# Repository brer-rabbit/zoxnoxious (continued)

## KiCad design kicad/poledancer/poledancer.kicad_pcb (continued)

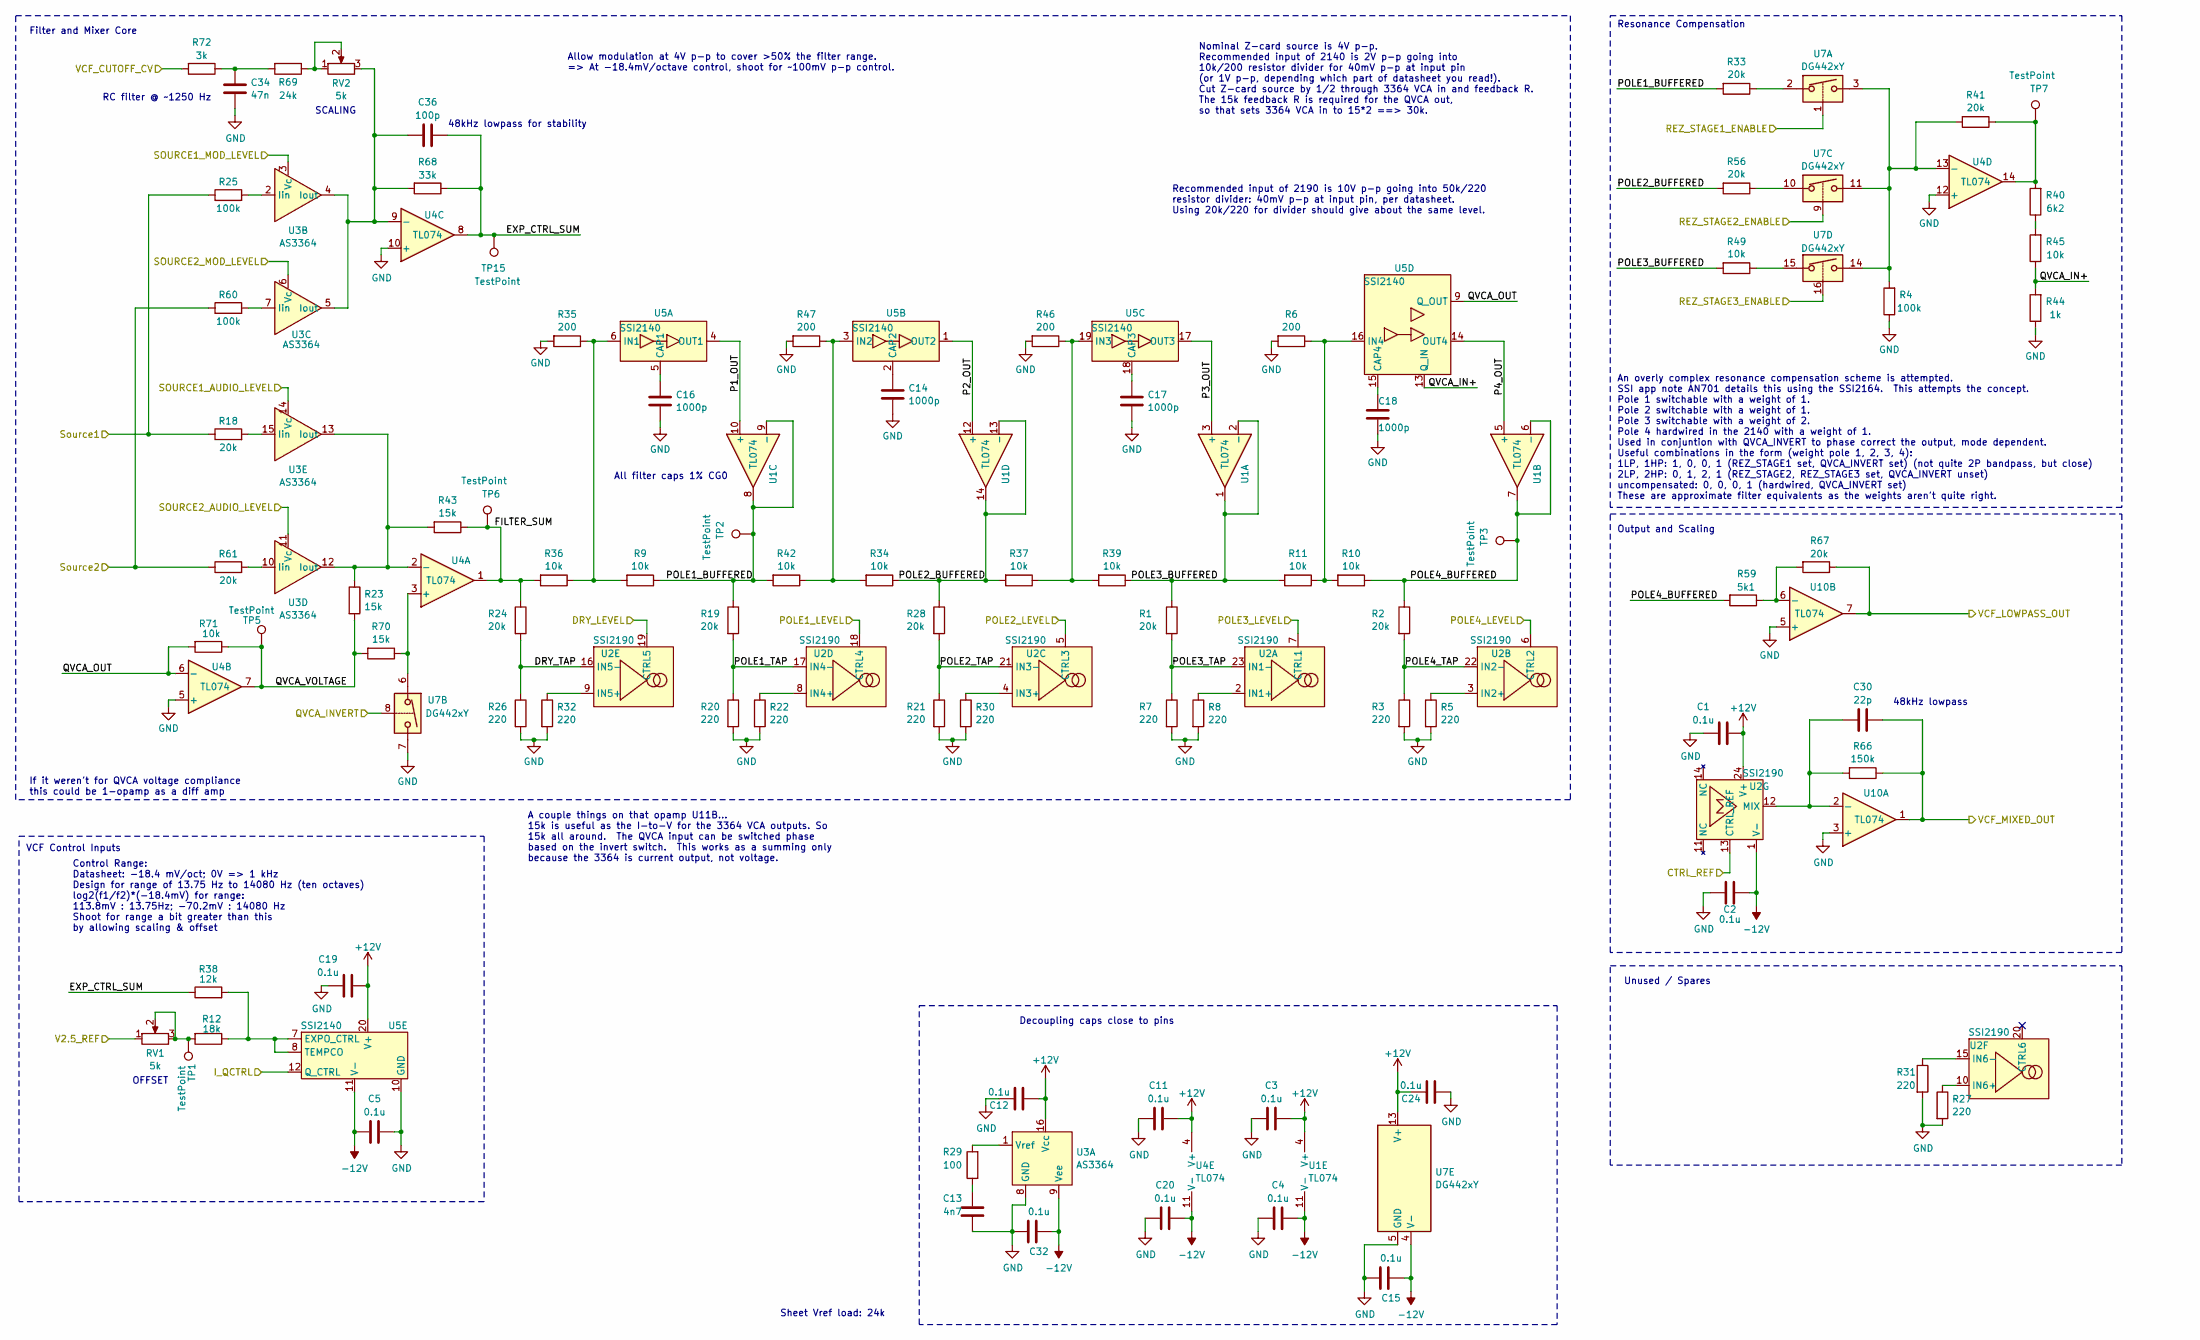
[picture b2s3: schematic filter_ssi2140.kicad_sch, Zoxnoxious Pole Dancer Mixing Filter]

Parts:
C1, C2, C3, C4, C5, C11, C12, C15, C19, C20, C24, C32: 0.1u; C_0603_1608Metric; LCSC C14663
C13: 4n7; C_0603_1608Metric; LCSC C53987
C14, C16, C17, C18: 1000p; C_0805_2012Metric; Digikey 478-KGM21BCG1H102FTCT-ND
C30: 22p; C_0603_1608Metric; LCSC C1653
C34: 47n; C_0603_1608Metric; LCSC C1622
C36: 100p; C_0603_1608Metric; LCSC C14858
R1, R2, R18, R19, R24, R28, R33, R41, R56, R61, R67: 20k; R_0603_1608Metric; LCSC C4184
R3, R5, R7, R8, R20, R21, R22, R26, R27, R30, R31, R32: 220; R_0603_1608Metric; LCSC C22962
R4, R25, R60: 100k; R_0603_1608Metric; LCSC C25803
R6, R35, R46, R47: 200; R_0603_1608Metric; LCSC C8218
R9, R10, R11, R34, R36, R37, R39, R42, R45, R49, R71: 10k; R_0603_1608Metric; LCSC C25804
R12: 18k; R_0603_1608Metric; LCSC C25810
R23, R43, R70: 15k; R_0603_1608Metric; LCSC C22809
R29: 100; R_0603_1608Metric; LCSC C22775
R38: 12k; R_0603_1608Metric; LCSC C22790
R40: 6k2; R_0603_1608Metric; LCSC C4260
R44: 1k; R_0603_1608Metric; LCSC C21190
R59: 5k1; R_0603_1608Metric; LCSC C23186
R66: 150k; R_0603_1608Metric; LCSC C22807
R68: 33k; R_0603_1608Metric; LCSC C4216
R69: 24k; R_0603_1608Metric; LCSC C23352
R72: 3k; R_0603_1608Metric; LCSC C4211
RV1, RV2: 5k; Potentiometer_Bourns_3296W_Vertical
TP1, TP2, TP3, TP5, TP6, TP7, TP15: TestPoint; TestPoint_Pad_2.0x2.0mm
U1, U4, U10: TL074; TSSOP-14_4.4x5mm_P0.65mm; LCSC C96507
U2: SSI2190; SSOP-24_3.9x8.7mm_P0.635mm
U3: AS3364; SOIC-16_3.9x9.9mm_P1.27mm
U5: SSI2140; SSOP-20_4.4x6.5mm_P0.65mm
U7: DG442xY; SOIC-16_3.9x9.9mm_P1.27mm; LCSC C2673321

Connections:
+12V: C1.1, C3.1, C11.1, C12.1, C19.1, C24.2, U1.4 (V+), U2.24 (V+), U3.16 (Vcc), U4.4 (V+), U5.20 (V+), U7.13 (V+); also elsewhere on the board
-12V: C2.1, C4.1, C5.2, C15.1, C20.1, C32.1, U1.11 (V-), U2.1 (V-), U3.9 (Vee), U4.11 (V-), U5.11 (V-), U7.4 (V-); also elsewhere on the board
/CTRL_REF: U2.13 (CTRL_REF); also elsewhere on the board
/DRY_LEVEL: U2.19 (CTRL5); also elsewhere on the board
/INPUT1: R18.1, R25.1; also elsewhere on the board
/INPUT2: R60.1, R61.1; also elsewhere on the board
/POLE1_LEVEL: U2.18 (CTRL4); also elsewhere on the board
/POLE2_LEVEL: U2.5 (CTRL3); also elsewhere on the board
/POLE3_LEVEL: U2.7 (CTRL1); also elsewhere on the board
/POLE4_LEVEL: U2.6 (CTRL2); also elsewhere on the board
/QCTRL_CURRENT: U5.12 (Q_CTRL); also elsewhere on the board
/QVCA_INVERT: U7.8; also elsewhere on the board
/REZ_STAGE1_EN: U7.1; also elsewhere on the board
/REZ_STAGE2_EN: U7.9; also elsewhere on the board
/REZ_STAGE3_EN: U7.16; also elsewhere on the board
/SOURCE1_AUDIO_CV: U3.14 (Vc); also elsewhere on the board
/SOURCE1_MOD_CV: U3.3 (Vc); also elsewhere on the board
/SOURCE2_AUDIO_CV: U3.11 (Vc); also elsewhere on the board
/SOURCE2_MOD_CV: U3.6 (Vc); also elsewhere on the board
/VCF_CUTOFF_CV: R72.2; also elsewhere on the board
/VCF_RAW: R67.1, U10.7; also elsewhere on the board
/VREF_2.5V: RV1.1; also elsewhere on the board
/filter_ssi2140/DRY_TAP: R24.2, R26.1, U2.16 (IN5-)
/filter_ssi2140/EXP_CTRL_SUM: C36.2, R38.1, R68.1, TP15.1, U4.8
/filter_ssi2140/FILTER_SUM: R24.1, R36.2, R43.1, TP6.1, U4.1
/filter_ssi2140/P1_OUT: U1.10 (+), U5.4 (OUT1)
/filter_ssi2140/P2_OUT: U1.12 (+), U5.1 (OUT2)
/filter_ssi2140/P3_OUT: U1.3 (+), U5.17 (OUT3)
/filter_ssi2140/P4_OUT: U1.5 (+), U5.14 (OUT4)
/filter_ssi2140/POLE1_BUFFERED: R9.1, R19.1, R33.2, R42.2, TP2.1, U1.8, U1.9 (-)
/filter_ssi2140/POLE1_TAP: R19.2, R20.1, U2.17 (IN4-)
/filter_ssi2140/POLE2_BUFFERED: R28.1, R34.1, R37.2, R56.2, U1.13 (-), U1.14
/filter_ssi2140/POLE2_TAP: R21.1, R28.2, U2.21 (IN3-)
/filter_ssi2140/POLE3_BUFFERED: R1.1, R11.2, R39.1, R49.2, U1.1, U1.2 (-)
/filter_ssi2140/POLE3_TAP: R1.2, R7.1, U2.23 (IN1-)
/filter_ssi2140/POLE4_BUFFERED: R2.1, R10.1, R59.2, TP3.1, U1.6 (-), U1.7
/filter_ssi2140/POLE4_TAP: R2.2, R3.1, U2.22 (IN2-)
/filter_ssi2140/QVCA_IN+: R44.2, R45.1, U5.13 (Q_IN)
/filter_ssi2140/QVCA_OUT: R71.2, U4.6 (-), U5.9 (Q_OUT)
/filter_ssi2140/QVCA_VOLTAGE: R23.2, R70.2, R71.1, TP5.1, U4.7
/filter_ssi2140/VCF_MIXED_OUT: C30.1, R66.1, U10.1; also elsewhere on the board
GND: C1.2, C2.2, C3.2, C4.2, C5.1, C11.2, C12.2, C13.2, C14.2, C15.2, C16.2, C17.2, C18.2, C19.2, C20.2, C24.1, C32.2, C34.2, R3.2, R4.1, R5.2, R6.2, R7.2, R8.2, R20.2, R21.2, R22.2, R26.2, R27.2, R30.2, R31.2, R32.2, R35.2, R44.1, R46.2, R47.2, U3.8 (GND), U4.5 (+), U4.10 (+), U4.12 (+), U5.10 (GND), U7.5 (GND), U7.7, U10.3 (+), U10.5 (+); also elsewhere on the board
unnamed: C13.1, R29.1
unnamed: C34.1, R69.2, R72.1
unnamed: R12.2, RV1.2, RV1.3, TP1.1
unnamed: R33.1, U7.2
unnamed: R40.1, R45.2
unnamed: R40.2, R41.1, TP7.1, U4.14
unnamed: R49.1, U7.15
unnamed: R56.1, U7.10
unnamed: R69.1, RV2.1, RV2.2
unnamed: R8.1, U2.2 (IN1+)
unnamed: R5.1, U2.3 (IN2+)
unnamed: R30.1, U2.4 (IN3+)
unnamed: R22.1, U2.8 (IN4+)
unnamed: R32.1, U2.9 (IN5+)
unnamed: R27.1, U2.10 (IN6+)
unnamed: R31.1, U2.15 (IN6-)
unnamed: R29.2, U3.1 (Vref)
unnamed: R25.2, U3.2 (Iin)
unnamed: C36.1, R68.2, RV2.3, U3.4 (Iout), U3.5 (Iout), U4.9 (-)
unnamed: R60.2, U3.7 (Iin)
unnamed: R61.2, U3.10 (Iin)
unnamed: R23.1, R43.2, U3.12 (Iout), U3.13 (Iout), U4.2 (-)
unnamed: R18.2, U3.15 (Iin)
unnamed: R70.1, U4.3 (+), U7.6
unnamed: R4.2, R41.2, U4.13 (-), U7.3, U7.11, U7.14
unnamed: C16.1, U5.5 (CAP1)
unnamed: R9.2, R35.1, R36.1, U5.6 (IN1)
unnamed: C14.1, U5.2 (CAP2)
unnamed: R34.2, R42.1, R47.1, U5.3 (IN2)
unnamed: C17.1, U5.18 (CAP3)
unnamed: R37.1, R39.2, R46.1, U5.19 (IN3)
unnamed: C18.1, U5.15 (CAP4)
unnamed: R6.1, R10.2, R11.1, U5.16 (IN4)
unnamed: R12.1, R38.2, U5.7 (EXPO_CTRL), U5.8 (TEMPCO)
unnamed: C30.2, R66.2, U2.12 (MIX), U10.2 (-)
unnamed: R59.1, R67.2, U10.6 (-)

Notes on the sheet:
Nominal Z-card source is 4V p-p. Recommended input of 2140 is 2V p-p going into 10k/200 resistor divider for 40mV p-p at input pin (or 1V p-p, depending which part of datasheet you read!). Cut Z-card source by 1/2 through 3364 VCA in and feedback R. The 15k feedback R is required for the QVCA out, 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
Allow modulation at 4V p-p to cover >50% the filter range. => At -18.4mV/octave control, shoot for ~100mV p-p control.
OFFSET
Decoupling caps close to pins
RC filter @ ~1250 Hz
Sheet Vref load: 24k
An overly complex resonance compensation scheme is attempted. SSI app note AN701 details this using the SSI2164. This attempts the concept. Pole 1 switchable with a weight of 1. Pole 2 switchable with a weight of 1. Pole 3 switchable with a weight of 2. Pole 4 hardwired in the 2140 with a weight of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
VCF Control Inputs
Output and Scaling
48kHz lowpass for stability
Unused / Spares
Recommended input of 2190 is 10V p-p going into 50k/220 resistor divider: 40mV p-p at input pin, per datasheet. Using 20k/220 for divider should give about the same level.
Control Range: Datasheet: -18.4 mV/oct; 0V => 1 kHz Design for range of 13.75 Hz to 14080 Hz (ten octaves) log2(f1/f2)*(-18.4mV) for range: 113.8mV : 13.75Hz; -70.2mV : 14080 Hz Shoot for range a bit greater than this by allowing scaling & offset
If it weren't for QVCA voltage compliance this could be 1-opamp as a diff amp
All filter caps 1% CG0
Filter and Mixer Core
48kHz lowpass
SCALING
A couple things on that opamp U11B... 15k is useful as the I-to-V for the 3364 VCA outputs. So 15k all around. The QVCA input can be switched phase based on the invert switch. This works as a summing only because the 3364 is current output, not voltage.
Resonance Compensation

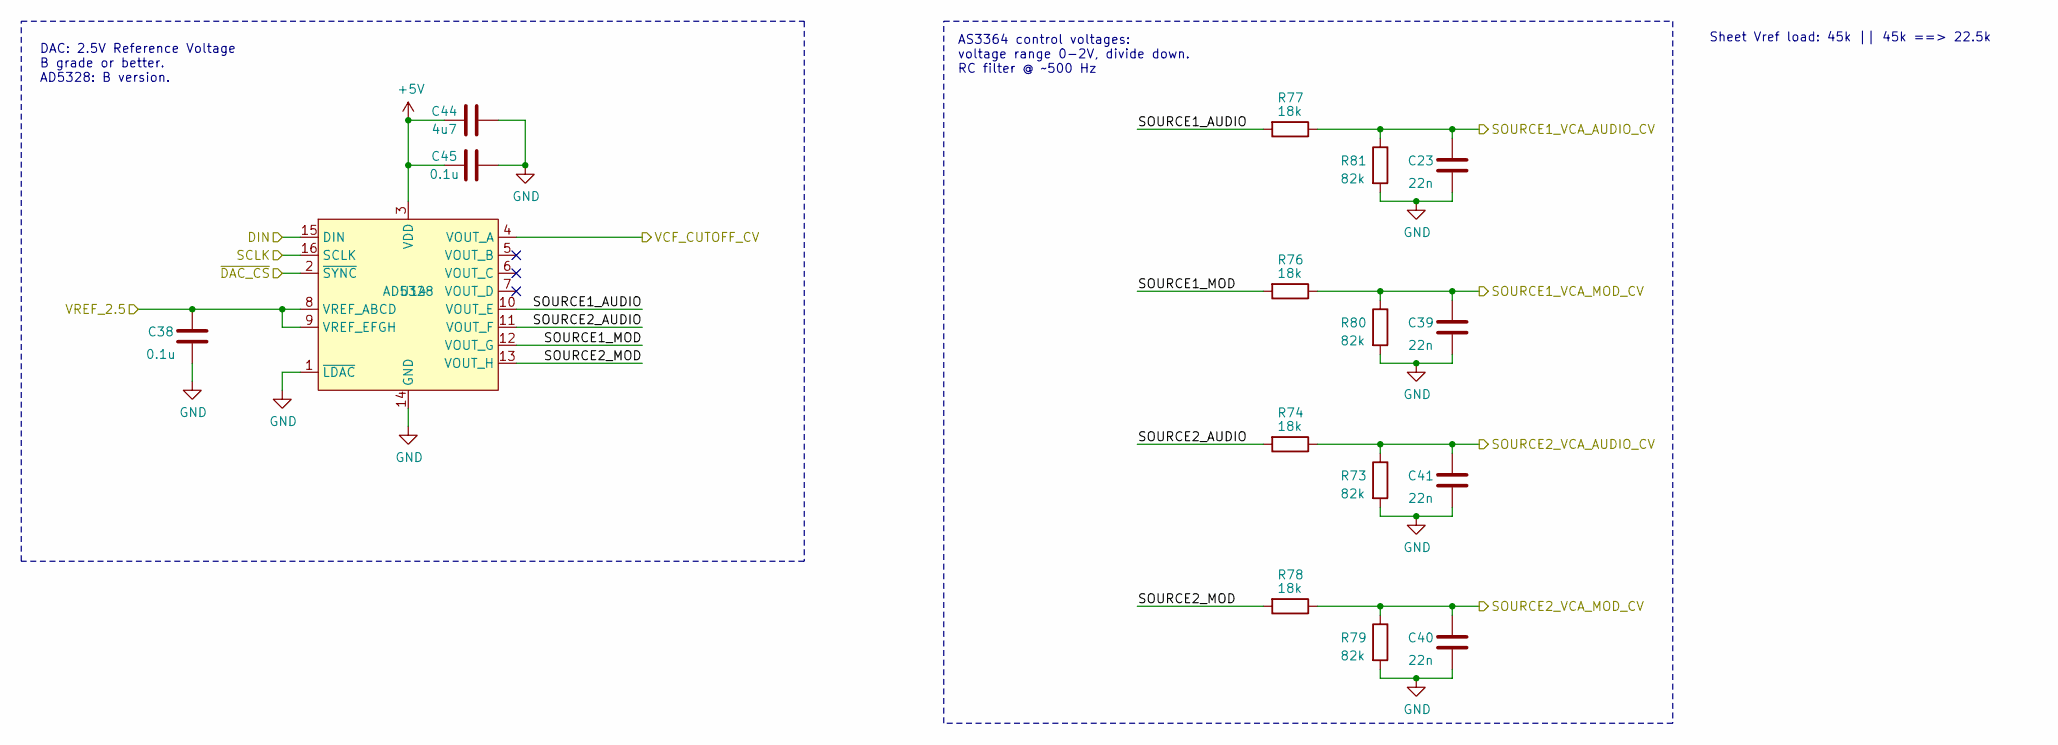
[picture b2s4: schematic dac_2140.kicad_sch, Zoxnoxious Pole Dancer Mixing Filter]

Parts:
C23, C39, C40, C41: 22n; C_0603_1608Metric; LCSC C21122
C38, C45: 0.1u; C_0603_1608Metric; LCSC C14663
C44: 4u7; C_0603_1608Metric; LCSC C19666
R73, R79, R80, R81: 82k; R_0603_1608Metric; LCSC C23254
R74, R76, R77, R78: 18k; R_0603_1608Metric; LCSC C25810
U14: AD5328; TSSOP-16_4.4x5mm_P0.65mm; LCSC C29162

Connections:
+5V: C44.1, C45.1, U14.3 (VDD); also elsewhere on the board
/SOURCE1_AUDIO_CV: C23.1, R77.1, R81.1; also elsewhere on the board
/SOURCE1_MOD_CV: C39.1, R76.1, R80.1; also elsewhere on the board
/SOURCE2_AUDIO_CV: C41.1, R73.1, R74.1; also elsewhere on the board
/SOURCE2_MOD_CV: C40.1, R78.1, R79.1; also elsewhere on the board
/SPI_CLK: U14.16 (SCLK); also elsewhere on the board
/SPI_CS0: U14.2 (~SYNC); also elsewhere on the board
/SPI_MOSI: U14.15 (DIN); also elsewhere on the board
/VCF_CUTOFF_CV: U14.4 (VOUT_A); also elsewhere on the board
/VREF_2.5V: C38.1, U14.8 (VREF_ABCD), U14.9 (VREF_EFGH); also elsewhere on the board
/dac_2140/SOURCE1_AUDIO: R77.2, U14.10 (VOUT_E)
/dac_2140/SOURCE1_MOD: R76.2, U14.12 (VOUT_G)
/dac_2140/SOURCE2_AUDIO: R74.2, U14.11 (VOUT_F)
/dac_2140/SOURCE2_MOD: R78.2, U14.13 (VOUT_H)
GND: C23.2, C38.2, C39.2, C40.2, C41.2, C44.2, C45.2, R73.2, R79.2, R80.2, R81.2, U14.1 (~LDAC), U14.14 (GND); also elsewhere on the board

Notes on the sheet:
AS3364 control voltages: voltage range 0-2V, divide down. RC filter @ ~500 Hz
DAC: 2.5V Reference Voltage B grade or better. AD5328: B version.
Sheet Vref load: 45k || 45k ==> 22.5k

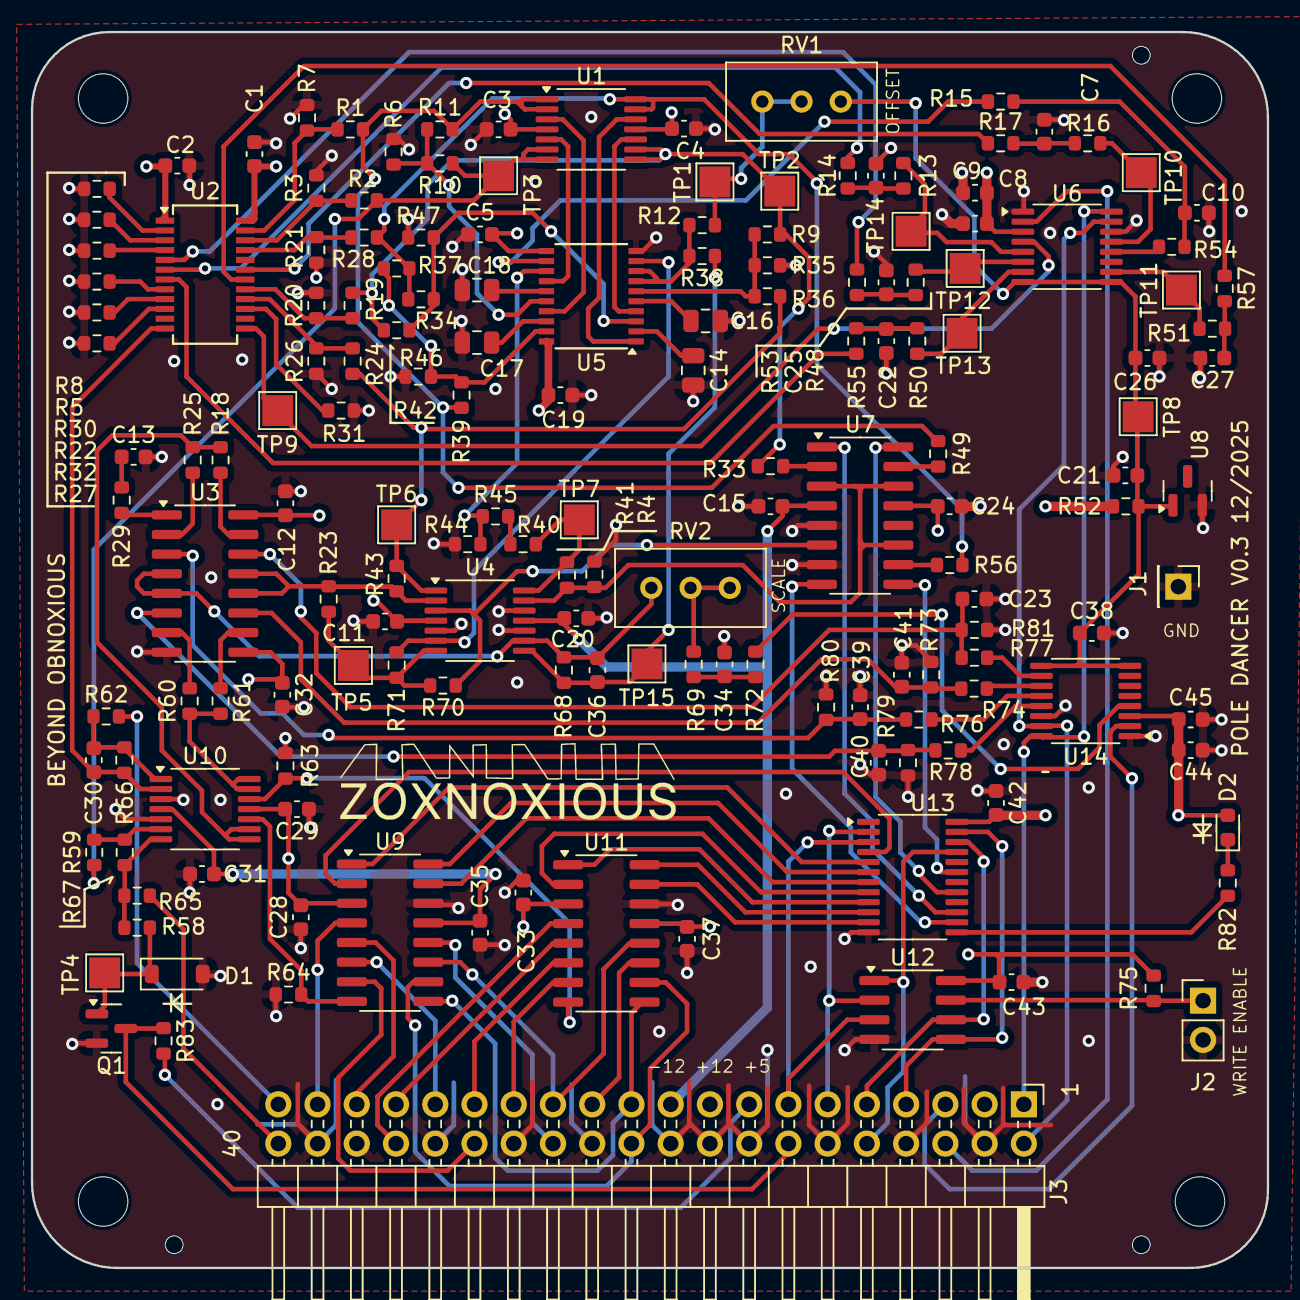
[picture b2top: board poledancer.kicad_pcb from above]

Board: 4 copper layers, 80.0 x 80.0 mm, 169 parts (0 on the bottom side), 134 nets.

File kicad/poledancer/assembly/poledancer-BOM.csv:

Comment,Designator,Footprint,LCPCB Part #
"4n7","C13","Capacitor_SMD:C_0603_1608Metric","C53987"
"2u2","C21","Capacitor_SMD:C_0603_1608Metric","C23630"
"22n","C23,C39,C40,C41","Capacitor_SMD:C_0603_1608Metric","C21122"
"0.1u","C1,C2,C3,C4,C5,C8,C10,C11,C12,C15,C19,C20,C24,C26,C28,C29,C31,C32,C33,C35,C37,C38,C42,C43,C45","Capacitor_SMD:C_0603_1608Metric","C14663"
"22p","C30","Capacitor_SMD:C_0603_1608Metric","C1653"
"100p","C36","Capacitor_SMD:C_0603_1608Metric","C14858"
"4u7","C9,C44","Capacitor_SMD:C_0603_1608Metric","C19666"
"47n","C6,C7,C22,C25,C27,C34","Capacitor_SMD:C_0603_1608Metric","C1622"
"1N4148W","D1","Diode_SMD:D_SOD-123","C81598"
"LED","D2","LED_SMD:LED_0603_1608Metric","C2286"
"MMBT3904","Q1","Package_TO_SOT_SMD:SOT-23","C20526"
"20k","R1,R2,R18,R19,R24,R28,R33,R41,R56,R61,R67","Resistor_SMD:R_0603_1608Metric","C4184"
"6k2","R13,R14,R16,R17,R40,R48,R50,R51,R53,R55,R57","Resistor_SMD:R_0603_1608Metric","C4260"
"3k9","R15,R54","Resistor_SMD:R_0603_1608Metric","C23018"
"15k","R23,R43,R70","Resistor_SMD:R_0603_1608Metric","C22809"
"100","R29","Resistor_SMD:R_0603_1608Metric","C22775"
"220","R3,R5,R7,R8,R20,R21,R22,R26,R27,R30,R31,R32","Resistor_SMD:R_0603_1608Metric","C22962"
"12k","R38","Resistor_SMD:R_0603_1608Metric","C22790"
"1k","R44","Resistor_SMD:R_0603_1608Metric","C21190"
"3k","R52,R72","Resistor_SMD:R_0603_1608Metric","C4211"
"100k","R4,R25,R58,R60,R63,R64","Resistor_SMD:R_0603_1608Metric","C25803"
"5k1","R59","Resistor_SMD:R_0603_1608Metric","C23186"
"200","R6,R35,R46,R47","Resistor_SMD:R_0603_1608Metric","C8218"
"51","R62,R65","Resistor_SMD:R_0603_1608Metric","C23197"
"150k","R66","Resistor_SMD:R_0603_1608Metric","C22807"
"33k","R68","Resistor_SMD:R_0603_1608Metric","C4216"
"24k","R69","Resistor_SMD:R_0603_1608Metric","C23352"
"82k","R73,R79,R80,R81","Resistor_SMD:R_0603_1608Metric","C23254"
"18k","R12,R74,R76,R77,R78","Resistor_SMD:R_0603_1608Metric","C25810"
"10k","R9,R10,R11,R34,R36,R37,R39,R42,R45,R49,R71,R75,R83","Resistor_SMD:R_0603_1608Metric","C25804"
"4k7","R82","Resistor_SMD:R_0603_1608Metric","C23162"
"TL074","U1,U4,U10","Package_SO:TSSOP-14_4.4x5mm_P0.65mm","C96507"
"M24C02-WMN","U12","Package_SO:SOIC-8_3.9x4.9mm_P1.27mm","C7562"
"PCA9555D","U13","Package_SO:TSSOP-24_4.4x7.8mm_P0.65mm","C83265"
"AD5328","U6,U14","Package_SO:TSSOP-16_4.4x5mm_P0.65mm","C29162"
"DG442xY","U7","Package_SO:SOIC-16_3.9x9.9mm_P1.27mm","C2673321"
"LM4040AIM3-2.5","U8","Package_TO_SOT_SMD:SOT-23","C111866"
"PS508","U9,U11","Package_SO:SOIC-16_3.9x9.9mm_P1.27mm","C2673104"

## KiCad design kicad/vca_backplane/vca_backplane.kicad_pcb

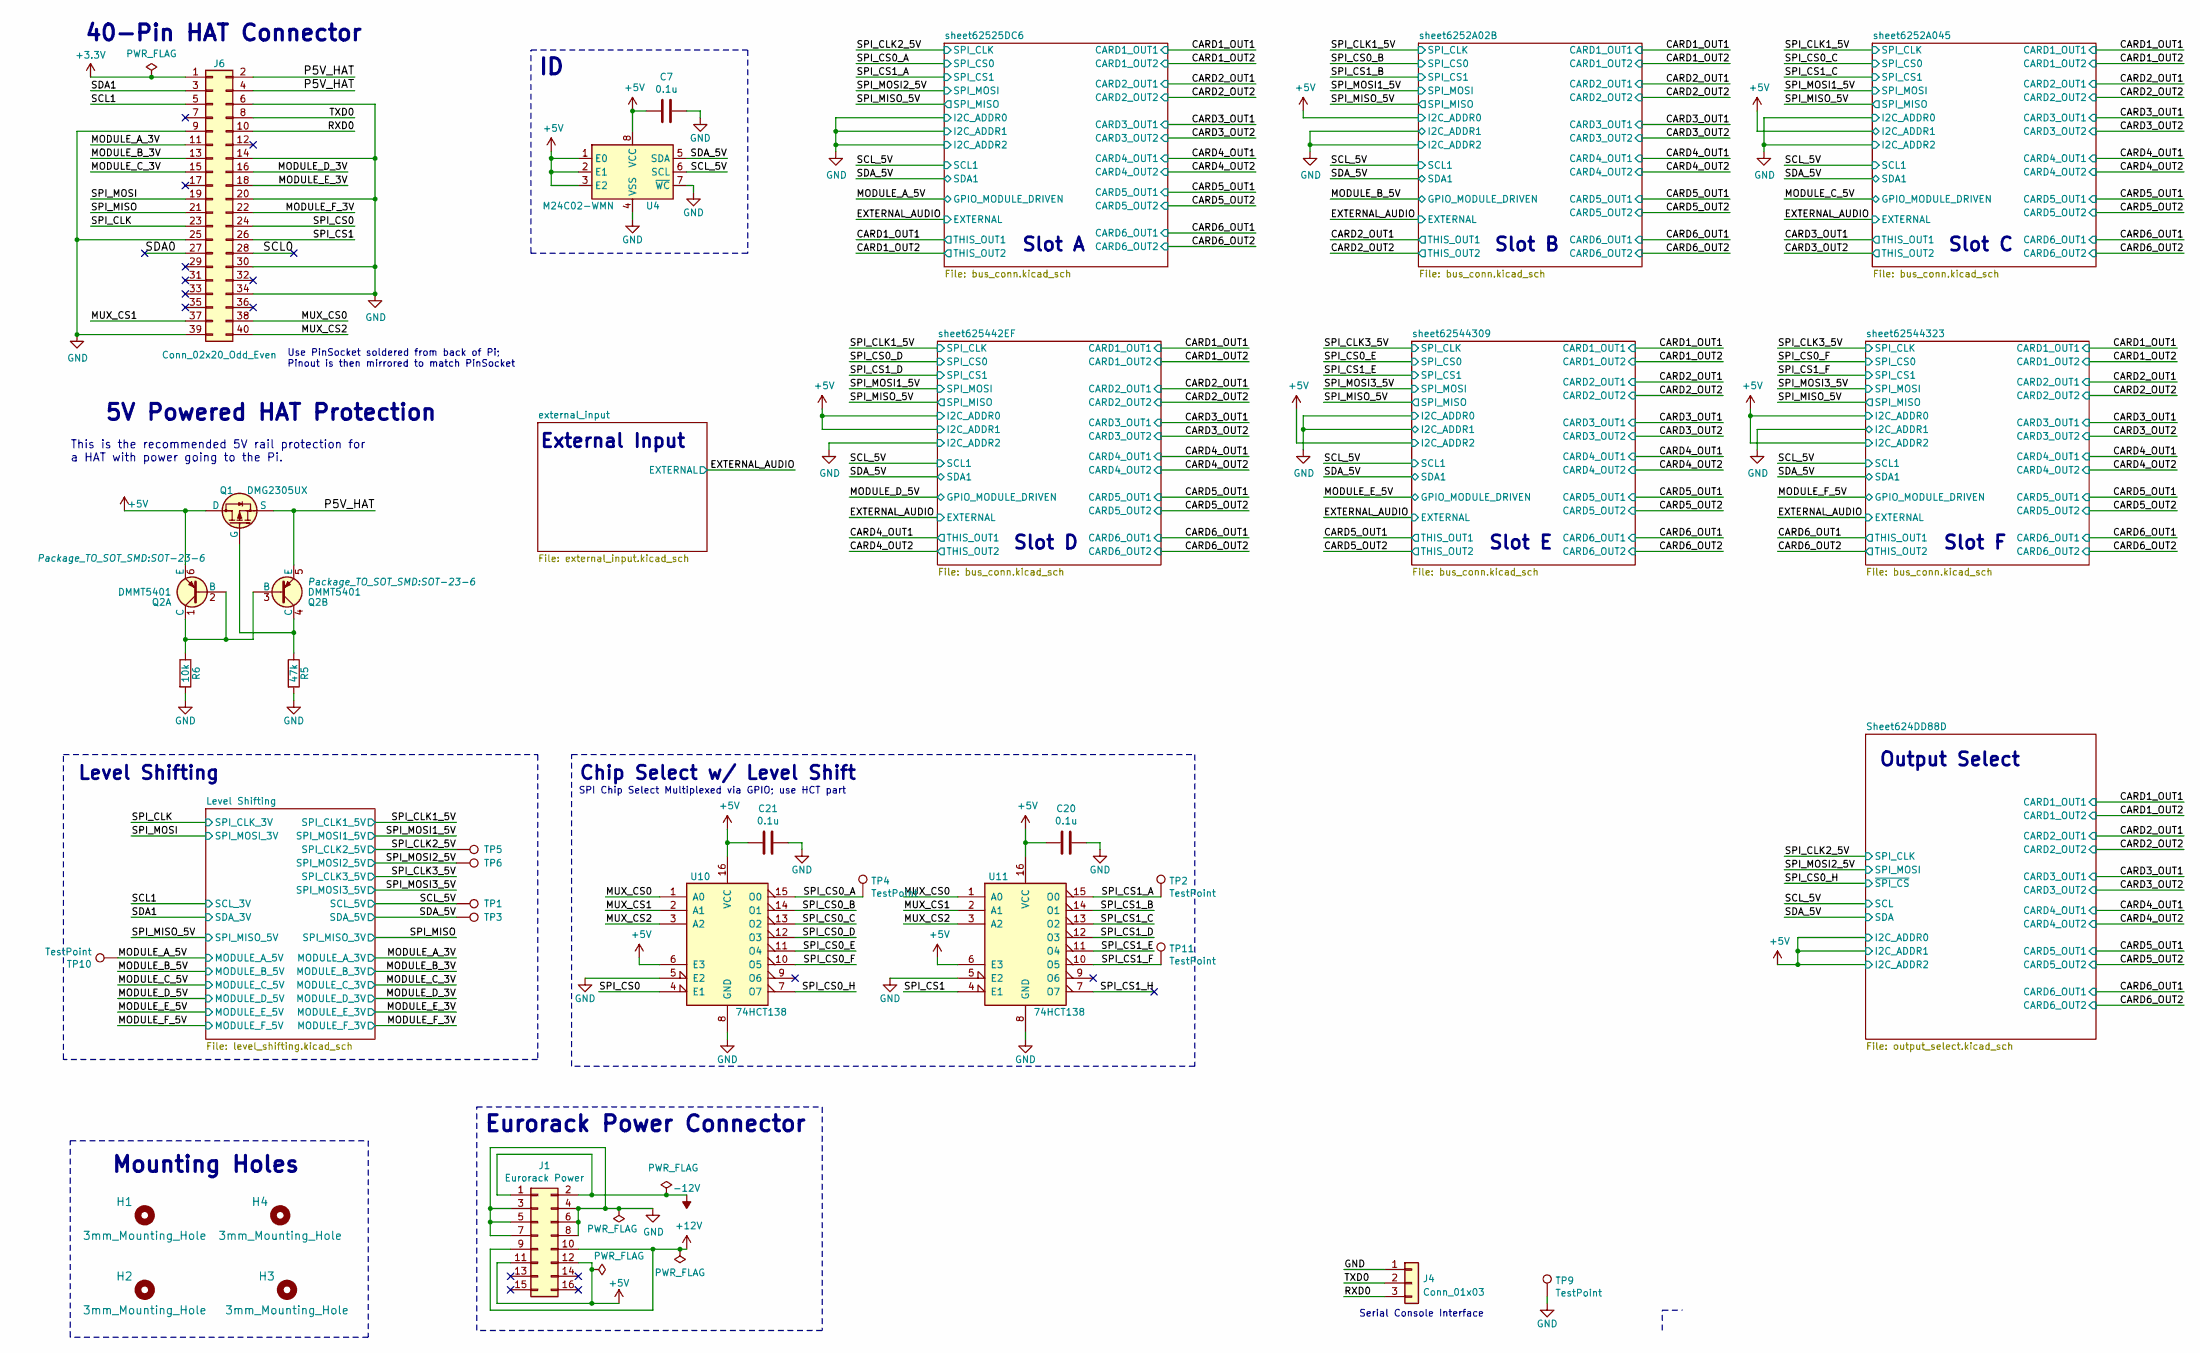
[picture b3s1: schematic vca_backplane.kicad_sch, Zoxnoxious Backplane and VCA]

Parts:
C7, C20, C21: 0.1u; C_0603_1608Metric; LCSC C14663
H1, H2, H3, H4: 3mm_Mounting_Hole; MountingHole_3.2mm_M3_Pad
J1: Eurorack Power; PinHeader_2x08_P2.54mm_ShroudedKey; Digikey S9171-ND
J4: Conn_01x03; PinHeader_1x03_P2.54mm_Vertical
J6: Conn_02x20_Odd_Even; PinHeader_2x20_P2.54mm_Vertical; Digikey S9200-ND
Q1: DMG2305UX; SOT-23-DMG2305UX; LCSC C150470
Q2: DMMT5401; SOT-23-6; LCSC C154733
R5: 47k; R_0603_1608Metric; LCSC C25819
R6: 10k; R_0603_1608Metric; LCSC C25804
TP1, TP2, TP3, TP4, TP5, TP6, TP10, TP11: TestPoint; TestPoint_Pad_2.0x2.0mm; Digikey 952-2664-2-ND
TP9: TestPoint; PinHeader_1x01_P2.54mm_Vertical; Digikey 952-2664-2-ND
U4: M24C02-WMN; SOIC-8_3.9x4.9mm_P1.27mm; LCSC C7562
U10, U11: 74HCT138; TSSOP-16_4.4x5mm_P0.65mm; LCSC C8115

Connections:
+3.3V: J6.1; also elsewhere on the board
+5V: C7.2, C20.2, C21.2, J1.11, J1.12, Q1.3 (D), Q2.6 (E), U4.1 (E0), U4.2 (E1), U4.3 (E2), U4.8 (VCC), U10.6 (E3), U10.16 (VCC), U11.6 (E3), U11.16 (VCC); also elsewhere on the board
+12V: J1.9, J1.10; also elsewhere on the board
-12V: J1.1, J1.2; also elsewhere on the board
/MODULE_A_3V: J6.11; also elsewhere on the board
/MODULE_A_5V: TP10.1; also elsewhere on the board
/MODULE_B_3V: J6.13; also elsewhere on the board
/MODULE_C_3V: J6.15; also elsewhere on the board
/MODULE_D_3V: J6.16; also elsewhere on the board
/MODULE_E_3V: J6.18; also elsewhere on the board
/MODULE_F_3V: J6.22; also elsewhere on the board
/MUX_CS0: J6.38, U10.1 (A0), U11.1 (A0)
/MUX_CS1: J6.37, U10.2 (A1), U11.2 (A1)
/MUX_CS2: J6.40, U10.3 (A2), U11.3 (A2)
/P5V_HAT: J6.2, J6.4, Q1.2 (S), Q2.5 (E)
/RXD0: J4.3, J6.10
/SCL0: J6.28
/SCL1: J6.5; also elsewhere on the board
/SCL_5V: TP1.1, U4.6 (SCL); also elsewhere on the board
/SDA0: J6.27
/SDA1: J6.3; also elsewhere on the board
/SDA_5V: TP3.1, U4.5 (SDA); also elsewhere on the board
/SPI_CLK: J6.23; also elsewhere on the board
/SPI_CLK2_5V: TP5.1; also elsewhere on the board
/SPI_CS0: J6.24, U10.4 (E1)
/SPI_CS0_A: TP4.1, U10.15 (O0); also elsewhere on the board
/SPI_CS0_B: U10.14 (O1); also elsewhere on the board
/SPI_CS0_C: U10.13 (O2); also elsewhere on the board
/SPI_CS0_D: U10.12 (O3); also elsewhere on the board
/SPI_CS0_E: U10.11 (O4); also elsewhere on the board
/SPI_CS0_F: U10.10 (O5); also elsewhere on the board
/SPI_CS0_H: U10.7 (O7); also elsewhere on the board
/SPI_CS1: J6.26, U11.4 (E1)
/SPI_CS1_A: TP2.1, U11.15 (O0); also elsewhere on the board
/SPI_CS1_B: U11.14 (O1); also elsewhere on the board
/SPI_CS1_C: U11.13 (O2); also elsewhere on the board
/SPI_CS1_D: U11.12 (O3); also elsewhere on the board
/SPI_CS1_E: U11.11 (O4); also elsewhere on the board
/SPI_CS1_F: TP11.1, U11.10 (O5); also elsewhere on the board
/SPI_CS1_H: U11.7 (O7)
/SPI_MISO: J6.21; also elsewhere on the board
/SPI_MOSI: J6.19; also elsewhere on the board
/SPI_MOSI2_5V: TP6.1; also elsewhere on the board
/TXD0: J4.2, J6.8
GND: C7.1, C20.1, C21.1, J1.3, J1.4, J1.5, J1.6, J1.7, J1.8, J4.1, J6.6, J6.9, J6.14, J6.20, J6.25, J6.30, J6.34, J6.39, R5.2, R6.2, TP9.1, U4.4 (VSS), U4.7 (~WC), U10.5 (E2), U10.8 (GND), U11.5 (E2), U11.8 (GND); also elsewhere on the board
unnamed: Q1.1 (G), Q2.4 (C), R5.1
unnamed: Q2.1 (C), Q2.2 (B), Q2.3 (B), R6.1

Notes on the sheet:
5V Powered HAT Protection
Slot A
External Input
Slot F
Level Shifting
Slot D
This is the recommended 5V rail protection for a HAT with power going to the Pi.
Serial Console Interface
Chip Select w/ Level Shift
Eurorack Power Connector
40-Pin HAT Connector
Output Select
Use PinSocket soldered from back of Pi; Pinout is then mirrored to match PinSocket
Slot C
Slot B
Mounting Holes
SPI Chip Select Multiplexed via GPIO; use HCT part
Slot E
